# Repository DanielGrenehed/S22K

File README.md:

# S22K
A 22 key split keyboard

# S20K
I started to use the keyboard with just 20 keys and with custom [keycaps](https://github.com/DanielGrenehed/keycaps/tree/main/Combiner)

## Firmware 
I currently run ZMK on this board. My config and layout can be found [here](https://github.com/DanielGrenehed/zmk-config/tree/master/config/boards/shields/s22k)

## HS22K
My previous design, the HS22K board is avaliable [here](https://github.com/DanielGrenehed/HS22K)

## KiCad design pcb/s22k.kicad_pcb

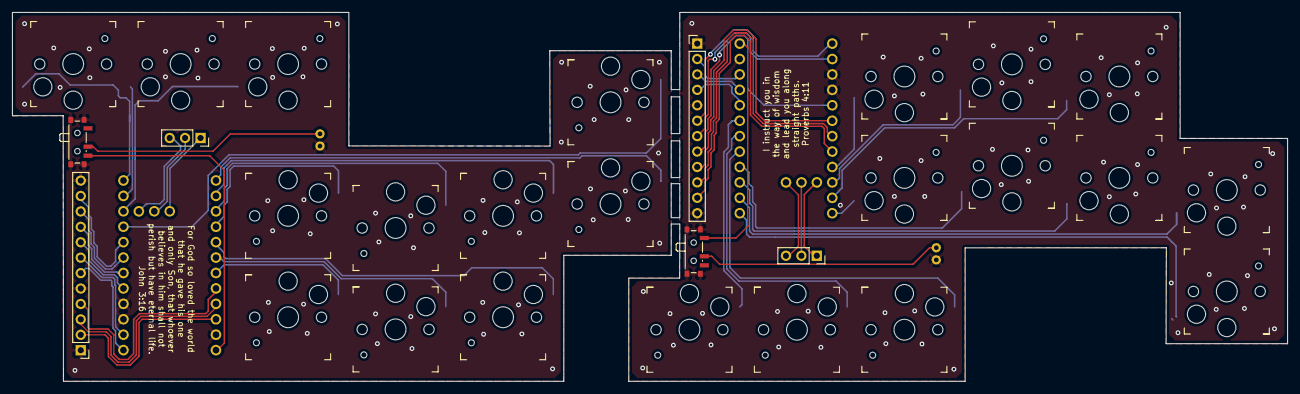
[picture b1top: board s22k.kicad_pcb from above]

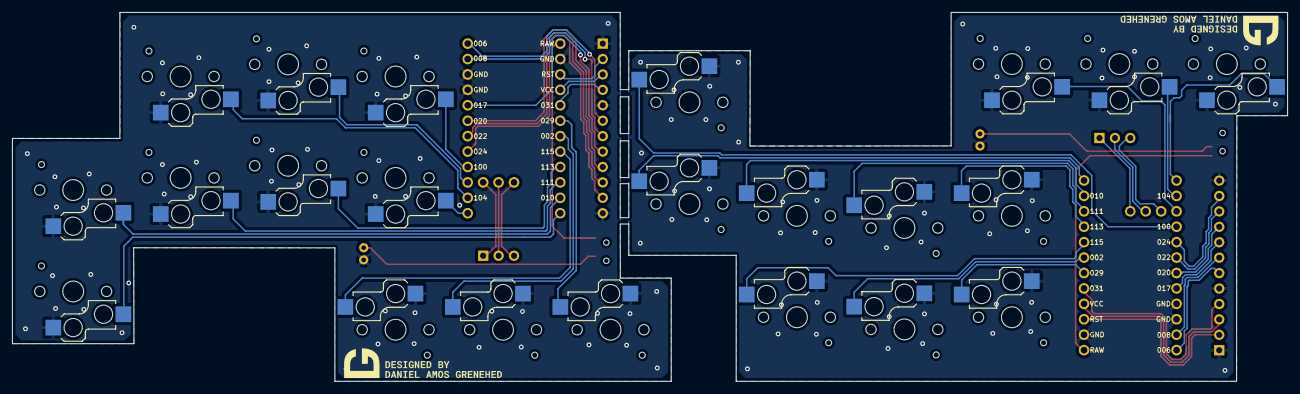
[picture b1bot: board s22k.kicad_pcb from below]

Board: 2 copper layers, 210.0 x 60.8 mm, 28 parts (2 on the bottom side), 45 nets.

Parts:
J1, J4: Conn_02x06_Odd_Even; PinHeader_1x12_P2.54mm_Vertical
J2, J3: Conn_01x03_Female; PinSocket_1x03_P2.54mm_Vertical
SW1, SW2, SW3, SW4, SW5, SW6, SW7, SW8, SW9, SW10, SW11, SW12, SW13, SW14, SW15, SW16, SW17, SW18, SW19, SW20, SW21, SW22: SW_SPST; Kailh_socket_PG1350
U1, U2: nice!nano; nice_nano

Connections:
/GND: J1.1, J1.5, J1.12, SW1.1 (A), SW2.1 (A), SW3.1 (A), SW4.1 (A), SW5.1 (A), SW6.1 (A), SW7.1 (A), SW8.1 (A), SW9.1 (A), SW10.1 (A), SW11.1 (A), U1.1 (GND)
/GND_L: J4.1, J4.5, J4.12, SW12.1 (A), SW13.1 (A), SW14.1 (A), SW15.1 (A), SW16.1 (A), SW17.1 (A), SW18.1 (A), SW19.1 (A), SW20.1 (A), SW21.1 (A), SW22.1 (A), U2.1 (GND)
unnamed: J1.2, U1.23 (RESET)
unnamed: J1.3, U1.22 (3.3V)
unnamed: J1.4, U1.21 (P0.31)
unnamed: J1.6, U1.2 (P0.06_TX0)
unnamed: J1.7, U1.3 (P0.08_RX0)
unnamed: J1.8, U1.6 (P0.17)
unnamed: J1.9, U1.7 (P0.20)
unnamed: J1.10, U1.8 (P0.22)
unnamed: J1.11, U1.9 (P0.24)
unnamed: J2.1, U1.26 (P1.01)
unnamed: J2.2, U1.27 (P1.02)
unnamed: J2.3, U1.28 (P1.07)
unnamed: J4.2, U2.23 (RESET)
unnamed: J4.3, U2.22 (3.3V)
unnamed: J4.4, U2.21 (P0.31)
unnamed: J4.6, U2.2 (P0.06_TX0)
unnamed: J4.7, U2.3 (P0.08_RX0)
unnamed: J4.8, U2.6 (GND)
unnamed: J4.9, U2.7 (P0.20)
unnamed: J4.10, U2.8 (P0.22)
unnamed: J4.11, U2.9 (P0.24)
unnamed: SW1.2 (B), U1.18 (P1.15)
unnamed: SW2.2 (B), U1.19 (P0.02)
unnamed: SW3.2 (B), U1.10 (P1.00)
unnamed: SW4.2 (B), U1.14 (P0.09)
unnamed: SW5.2 (B), U1.20 (P0.29)
unnamed: SW6.2 (B), U1.11 (P0.11)
unnamed: SW7.2 (B), U1.15 (P0.10)
unnamed: SW8.2 (B), U1.12 (P1.04)
unnamed: SW9.2 (B), U1.16 (P1.11)
unnamed: SW10.2 (B), U1.13 (P1.06)
unnamed: SW11.2 (B), U1.17 (P1.13)
unnamed: SW12.2 (B), U2.18 (P1.15)
unnamed: SW13.2 (B), U2.19 (P0.02)
unnamed: SW14.2 (B), U2.10 (P1.00)
unnamed: SW15.2 (B), U2.14 (P0.09)
unnamed: SW16.2 (B), U2.20 (P0.29)
unnamed: SW17.2 (B), U2.11 (P0.11)
unnamed: SW18.2 (B), U2.15 (P0.10)
unnamed: SW19.2 (B), U2.12 (P1.04)
unnamed: SW20.2 (B), U2.16 (P1.11)
unnamed: SW21.2 (B), U2.13 (P1.06)
unnamed: SW22.2 (B), U2.17 (P1.13)

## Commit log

2022-11-07 added pcb
2022-11-09 pictures
2026-03-23 Added s20k case
2026-03-23 Added case readme
2026-03-23 case naming explained
2026-03-23 added keycap link
2026-03-23 fixed keycap link
2026-03-23 fixed wording in case/README
